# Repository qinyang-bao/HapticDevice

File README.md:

# HapticDevice
2A URA, a device to provide haptic feedback

This project aims to control 6 vibration motors individually to construct different haptic feedback patterns, using an Arduino.  
  
This is achieved by leveraging the power of drv2603 haptic driver, which takes a PWM signal as input and convert it to appropriate signals
for ERM/LRA vibration motors. The challenge is that the PWM signal needs to be at least 10 kHz, which is much faster than the analogWrite (a easy way to simulate PWM signals). Therefore, one must fiddle with the timer registers and use fast PWM. Also, since there are 3 timers on the ATmega328P processor each able to control 2 outputs, a total of 6 motors might be controlled separately.    

Currently, the software aspect (first version) of this project has been developped and tested. The next step is to finish and verify
the electrical and mechanical designs.    

The CAD of individual enclosing for the 307-100 vibration motor and the KiCad files for the breakout board for the drv2603 are also included in this repo.

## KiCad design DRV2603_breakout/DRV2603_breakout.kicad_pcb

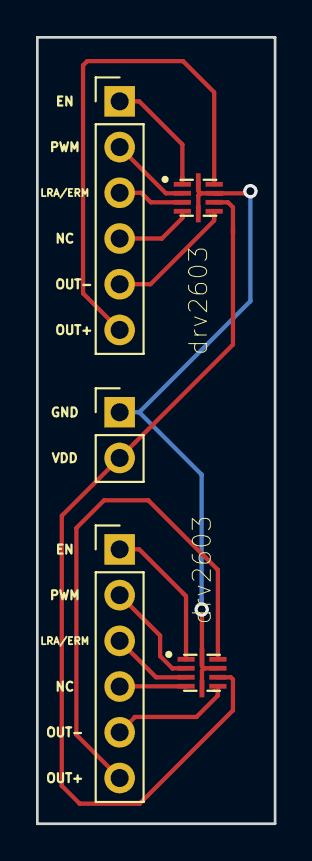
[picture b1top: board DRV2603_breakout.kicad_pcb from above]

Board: 2 copper layers, 13.2 x 43.7 mm, 5 parts (0 on the bottom side), 14 nets.

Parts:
J1: Conn_01x02_Male; PinHeader_1x02_P2.54mm_Vertical
J2, J3: Conn_01x06_Male; PinHeader_1x06_P2.54mm_Vertical
U1, U2: drv2603; QFN50P200X200X80-10N

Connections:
/EN: J2.1, U1.1
/EN_2: J3.1, U2.1
/GND: J1.1, U1.5, U1.8, U1.10, U2.5, U2.8, U2.10
/LRA_ERM: J2.3, U1.3
/LRA_ERM_2: J3.3, U2.3
/NC: J2.4, U1.4
/NC_2: J3.4, U2.4
/OUT+: J2.6, U1.9
/OUT+_2: J3.6, U2.9
/OUT-: J2.5, U1.6
/OUT-_2: J3.5, U2.6
/PWM: J2.2, U1.2
/PWM_2: J3.2, U2.2
/VDD: J1.2, U1.7, U2.7

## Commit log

2018-11-19 init
2018-11-19 change read me
2018-12-28 add circuits and datasheet
2019-01-03 added solidworks and LRA motor reference
